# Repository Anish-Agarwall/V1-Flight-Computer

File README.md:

# V1 Flight Computer

An STM32-based rocket flight computer designed by Anish Agarwal and Aidan Gonzales. This repository contains the KiCad schematics and PCB layout, custom component libraries, and firmware developed in STM32CubeIDE.

The board brings together flight sensing, GPS, LoRa telemetry, microSD logging, main and drogue deployment channels, and a servo output for airbrakes.

## Hardware

The PCB uses four copper layers and an STM32F446RE microcontroller.

| Component | Purpose | Firmware interface |
| --- | --- | --- |
| BMI088 | Accelerometer and gyroscope | I2C1 |
| BMP388 | Pressure, temperature, and barometric altitude | I2C1 |
| LIS3MDL | Magnetometer | I2C1 |
| u-blox NEO-M9N | GPS | USART6 |
| E22-900MM22S | LoRa telemetry | SPI1 |
| W25Q128JVS | 128-Mbit external flash | SPI2 |
| microSD | CSV data logging | SPI3 |

The design also includes battery-voltage and deployment-continuity sensing, a buzzer, a heartbeat LED, and USB-C. The active firmware uses the BMI088; a BMI330 driver is also included in the source tree.

## Firmware

The application is written in C using the STM32 HAL and FatFs. Most of the flight logic is in [`main.c`](V1_STM32/Core/Src/main.c), with separate drivers for the sensors, GPS, radio, SD card, and flash.

The main loop handles:

- Sensor readings and flight-state updates on a nominal 50 ms interval.
- Ground-relative barometric altitude, filtered altitude, and estimated vertical velocity.
- Launch and apogee detection, followed by drogue and main deployment states.
- GPS stream processing and LoRa packet transmission, scheduled at 200 ms intervals.
- Buffered CSV logging to the SD card.
- Servo airbrake control using predicted apogee and a PD controller, enabled seven seconds after launch.

Flight thresholds, deployment settings, and servo limits are defined in `main.c`. The airbrake target and controller gains are inside `Task_Airbrakes()`.

### Data logging

On startup, the firmware selects a numbered log file such as `LOG_0.CSV` or `LOG_1.CSV`. Logged fields include altitude, pressure, temperature, flight state, airbrake output, filtered altitude and velocity, magnetometer readings, and GPS data.

Battery and continuity columns are present, but their periodic sampling task is currently commented out. Data rows also include a Unix timestamp that is missing from the startup CSV header.

The flash driver and a binary logging routine are included, but the current main loop uses the SD logging path and does not call the flash-log flush routine.

## Repository layout

| Path | Contents |
| --- | --- |
| `V1_Hardware/` | KiCad project, schematics, PCB layout, footprints, and 3D models |
| `V1_STM32/` | STM32CubeIDE project and CubeMX configuration |
| `V1_STM32/Core/Src/` | Main application and device drivers |
| `V1_STM32/Core/Inc/` | Headers, telemetry packet definitions, and buffer utilities |
| `V1_STM32/FATFS/` | FatFs configuration and SD disk interface |
| `V1_STM32/Drivers/` | STM32 HAL and CMSIS files |
| `LRA_Parts/` | Component symbols, footprints, and models |

## Opening the project

### Hardware

1. Open `V1_Hardware/V1.kicad_pro` in KiCad. The checked-in design files were saved with KiCad 10.0.
2. In **Preferences → Configure Paths**, set `LRA_PARTS` to the repository's `LRA_Parts` directory.
3. Check the project symbol-library table. Some entries still use absolute Windows paths and need to be pointed to your local copies. Entries that point to a directory should be updated to the corresponding `.kicad_sym` file.

The root schematic is `V1.kicad_sch`. Separate sheets cover power, deployment circuitry, USB-C, memory, GPS/telemetry, and sensors.

### Firmware

1. In STM32CubeIDE, choose **File → Import → General → Existing Projects into Workspace** and select `V1_STM32`.
2. Build the imported project. The repository includes the HAL, CMSIS, and FatFs sources.
3. Use an ST-LINK connection over SWD to program and debug the board. Check the probe settings in the included `V1 Debug.launch` configuration for your setup.

`V1.ioc` contains the CubeMX configuration and records STM32CubeMX 6.14.1 with STM32CubeF4 firmware package V1.28.3. Check the existing application code before regenerating peripheral initialization code.

## Development notes

Some earlier bring-up routines and alternate logging paths remain in the source. Follow the active calls in `main.c` when checking current behavior; a few older comments describe previous pin assignments or hardware revisions.

The `LANDED` state currently follows the main-deployment timer rather than a separate touchdown detector.

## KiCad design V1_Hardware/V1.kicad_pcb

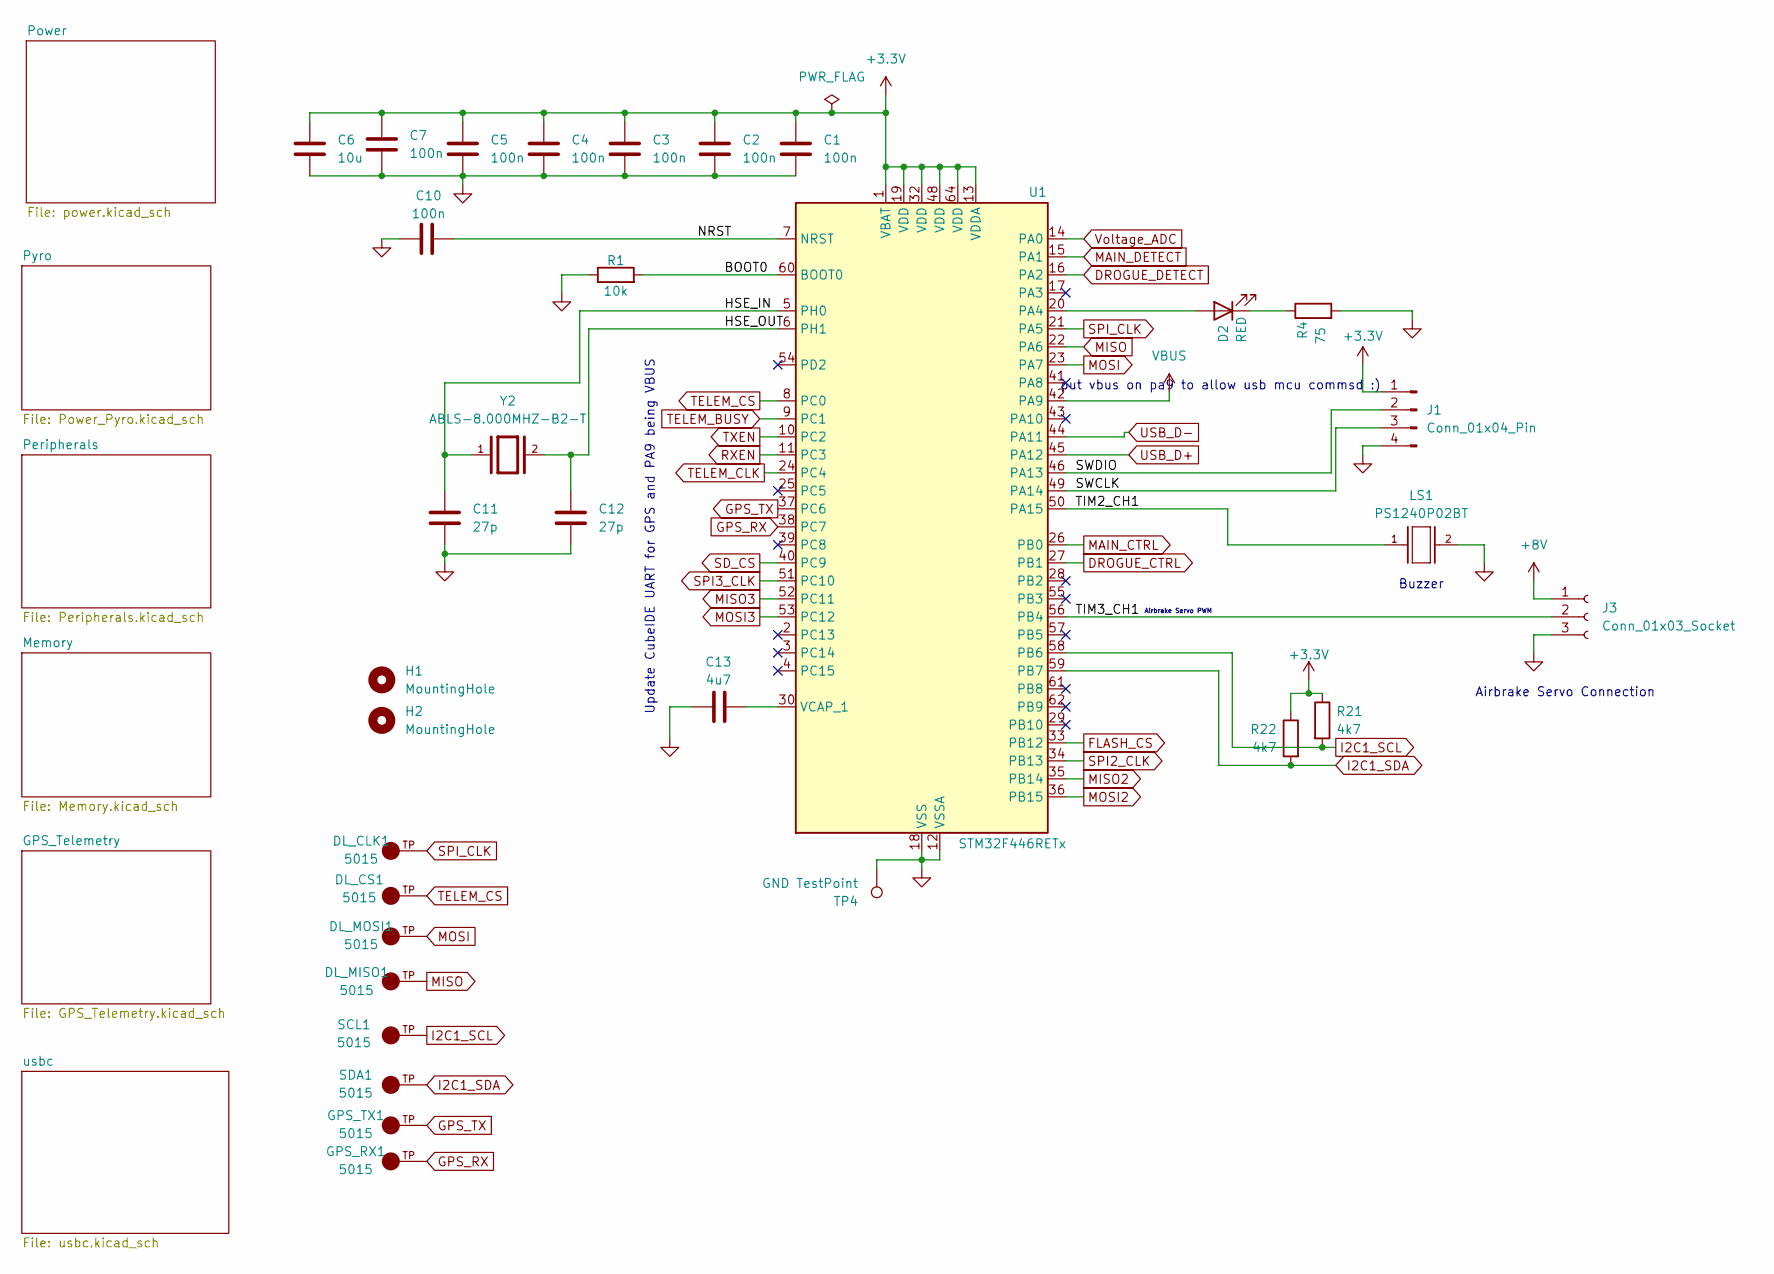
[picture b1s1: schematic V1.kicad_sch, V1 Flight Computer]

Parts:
C1, C2, C3, C4, C5, C7, C10: 100n; C_0603_1608Metric_Pad1.08x0.95mm_HandSolder
C6: 10u; C_0603_1608Metric_Pad1.08x0.95mm_HandSolder
C11, C12: 27p; C_0603_1608Metric_Pad1.08x0.95mm_HandSolder
C13: 4u7; C_0603_1608Metric_Pad1.08x0.95mm_HandSolder
D2: RED; LED_1206_3216Metric_Pad1.42x1.75mm_HandSolder
DL_CLK1: 5015; PARTREV F
DL_CS1: 5015; PARTREV F
DL_MISO1: 5015; PARTREV F
DL_MOSI1: 5015; PARTREV F
GPS_RX1: 5015; PARTREV F
GPS_TX1: 5015; PARTREV F
H1, H2: MountingHole; MountingHole_3.2mm_M3
J1: Conn_01x04_Pin; PinHeader_1x04_P2.54mm_Vertical
J3: Conn_01x03_Socket; Molex_Nano-Fit_105309-xx03_1x03_P2.50mm_Vertical
LS1: PS1240P02BT
R1: 10k; R_0603_1608Metric_Pad0.98x0.95mm_HandSolder
R4: 75; R_0603_1608Metric_Pad0.98x0.95mm_HandSolder
R21, R22: 4k7; R_0603_1608Metric_Pad0.98x0.95mm_HandSolder
SCL1: 5015; PARTREV F
SDA1: 5015; PARTREV F
TP4: GND TestPoint; TestPoint_Pad_D2.0mm
U1: STM32F446RETx; LQFP-64_10x10mm_P0.5mm
Y2: ABLS-8.000MHZ-B2-T; PARTREV 02.16.2021

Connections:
+3.3V: C1.1, C2.1, C3.1, C4.1, C5.1, C6.1, C7.1, J1.1, R21.1, R22.1, U1.1 (VBAT), U1.13 (VDDA), U1.19 (VDD), U1.32 (VDD), U1.48 (VDD), U1.64 (VDD); also elsewhere on the board
+8V: J3.1; also elsewhere on the board
/BOOT0: R1.2, U1.60 (BOOT0)
/HSE_IN: C11.1, U1.5 (PH0), Y2.1
/HSE_OUT: C12.1, U1.6 (PH1), Y2.2
/NRST: C10.2, U1.7 (NRST)
/SWCLK: J1.3, U1.49 (PA14)
/SWDIO: J1.2, U1.46 (PA13)
/TIM2_CH1: LS1.1, U1.50 (PA15)
/TIM3_CH1: J3.2, U1.56 (PB4)
DROGUE_CTRL: U1.27 (PB1); also elsewhere on the board
DROGUE_DETECT: U1.16 (PA2); also elsewhere on the board
FLASH_CS: U1.33 (PB12); also elsewhere on the board
GND: C1.2, C2.2, C3.2, C4.2, C5.2, C6.2, C7.2, C10.1, C11.2, C12.2, C13.1, J1.4, J3.3, LS1.2, R1.1, R4.2, TP4.1 (1_1), U1.12 (VSSA), U1.18 (VSS), U1.31 (VSS), U1.47 (VSS), U1.63 (VSS); also elsewhere on the board
GPS_RX: GPS_RX1.TP, U1.38 (PC7); also elsewhere on the board
GPS_TX: GPS_TX1.TP, U1.37 (PC6); also elsewhere on the board
I2C1_SCL: R21.2, SCL1.TP, U1.58 (PB6); also elsewhere on the board
I2C1_SDA: R22.2, SDA1.TP, U1.59 (PB7); also elsewhere on the board
MAIN_CTRL: U1.26 (PB0); also elsewhere on the board
MAIN_DETECT: U1.15 (PA1); also elsewhere on the board
MISO: DL_MISO1.TP, U1.22 (PA6); also elsewhere on the board
MISO2: U1.35 (PB14); also elsewhere on the board
MISO3: U1.52 (PC11); also elsewhere on the board
MOSI: DL_MOSI1.TP, U1.23 (PA7); also elsewhere on the board
MOSI2: U1.36 (PB15); also elsewhere on the board
MOSI3: U1.53 (PC12); also elsewhere on the board
unnamed: D2.2 (A), U1.20 (PA4)
unnamed: D2.1 (K), R4.1
unnamed: C13.2, U1.30 (VCAP_1)
RXEN: U1.11 (PC3); also elsewhere on the board
SD_CS: U1.40 (PC9); also elsewhere on the board
SPI2_CLK: U1.34 (PB13); also elsewhere on the board
SPI3_CLK: U1.51 (PC10); also elsewhere on the board
SPI_CLK: DL_CLK1.TP, U1.21 (PA5); also elsewhere on the board
TELEM_BUSY: U1.9 (PC1); also elsewhere on the board
TELEM_CLK: U1.24 (PC4); also elsewhere on the board
TELEM_CS: DL_CS1.TP, U1.8 (PC0); also elsewhere on the board
TXEN: U1.10 (PC2); also elsewhere on the board
USB_D+: U1.45 (PA12); also elsewhere on the board
USB_D-: U1.44 (PA11); also elsewhere on the board
VBUS: U1.42 (PA9); also elsewhere on the board
Voltage_ADC: U1.14 (PA0); also elsewhere on the board

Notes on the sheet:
Update CubeIDE UART for GPS and PA9 being VBUS
put vbus on pa9 to allow usb mcu commsd :)
Airbrake Servo Connection
Airbrake Servo PWM
Buzzer

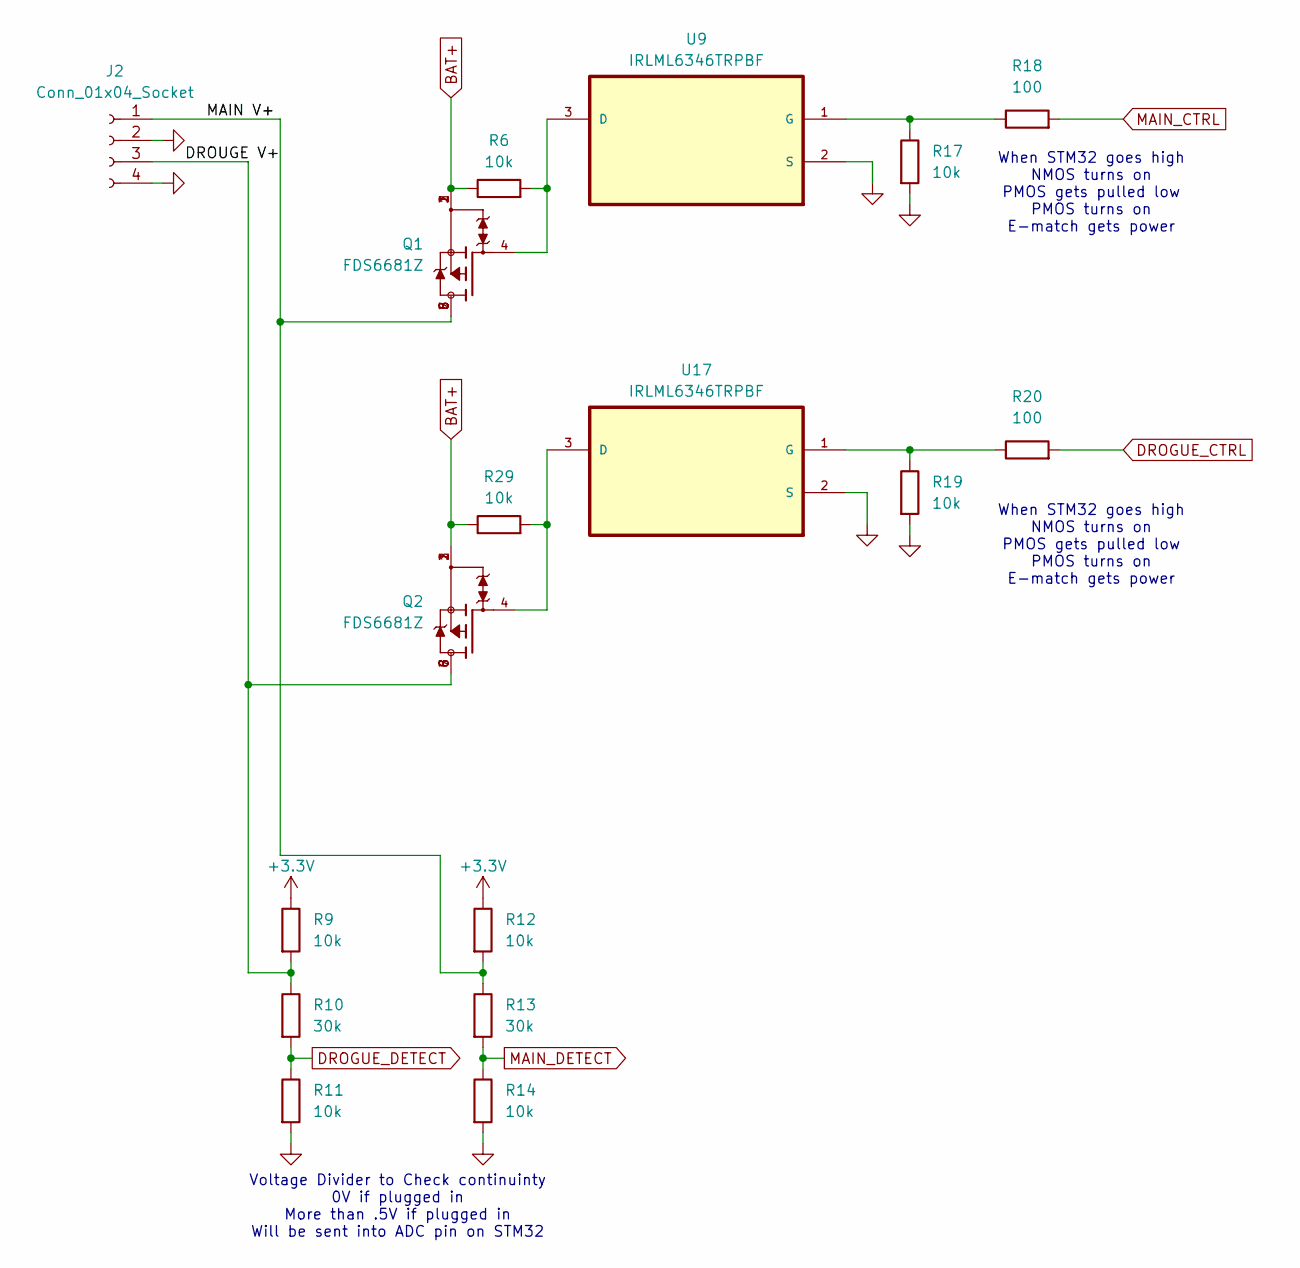
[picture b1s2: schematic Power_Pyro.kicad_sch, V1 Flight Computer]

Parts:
J2: Conn_01x04_Socket; Molex_Nano-Fit_105309-xx04_1x04_P2.50mm_Vertical
Q1, Q2: FDS6681Z
R6, R9, R11, R12, R14, R17, R19, R29: 10k; R_0603_1608Metric_Pad0.98x0.95mm_HandSolder
R10, R13: 30k; R_0603_1608Metric_Pad0.98x0.95mm_HandSolder
R18, R20: 100; R_0603_1608Metric_Pad0.98x0.95mm_HandSolder
U9, U17: IRLML6346TRPBF; MPN IRLML6346TRPBF

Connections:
+3.3V: R9.1, R12.1; also elsewhere on the board
/Pyro/DROUGE V+: J2.3, Q2.5, Q2.6, Q2.7, Q2.8, R9.2, R10.1
/Pyro/MAIN V+: J2.1, Q1.5, Q1.6, Q1.7, Q1.8, R12.2, R13.1
BAT+: Q1.1, Q1.2, Q1.3, Q2.1, Q2.2, Q2.3, R6.1, R29.1; also elsewhere on the board
DROGUE_CTRL: R20.2; also elsewhere on the board
DROGUE_DETECT: R10.2, R11.1; also elsewhere on the board
GND: J2.2, J2.4, R11.2, R14.2, R17.2, R19.2, U9.2 (S), U17.2 (S); also elsewhere on the board
MAIN_CTRL: R18.2; also elsewhere on the board
MAIN_DETECT: R13.2, R14.1; also elsewhere on the board
unnamed: Q1.4, R6.2, U9.3 (D)
unnamed: R17.1, R18.1, U9.1 (G)
unnamed: Q2.4, R29.2, U17.3 (D)
unnamed: R19.1, R20.1, U17.1 (G)

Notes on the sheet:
Voltage Divider to Check continuinty 0V if plugged in More than .5V if plugged in Will be sent into ADC pin on STM32
When STM32 goes high NMOS turns on PMOS gets pulled low PMOS turns on E-match gets power

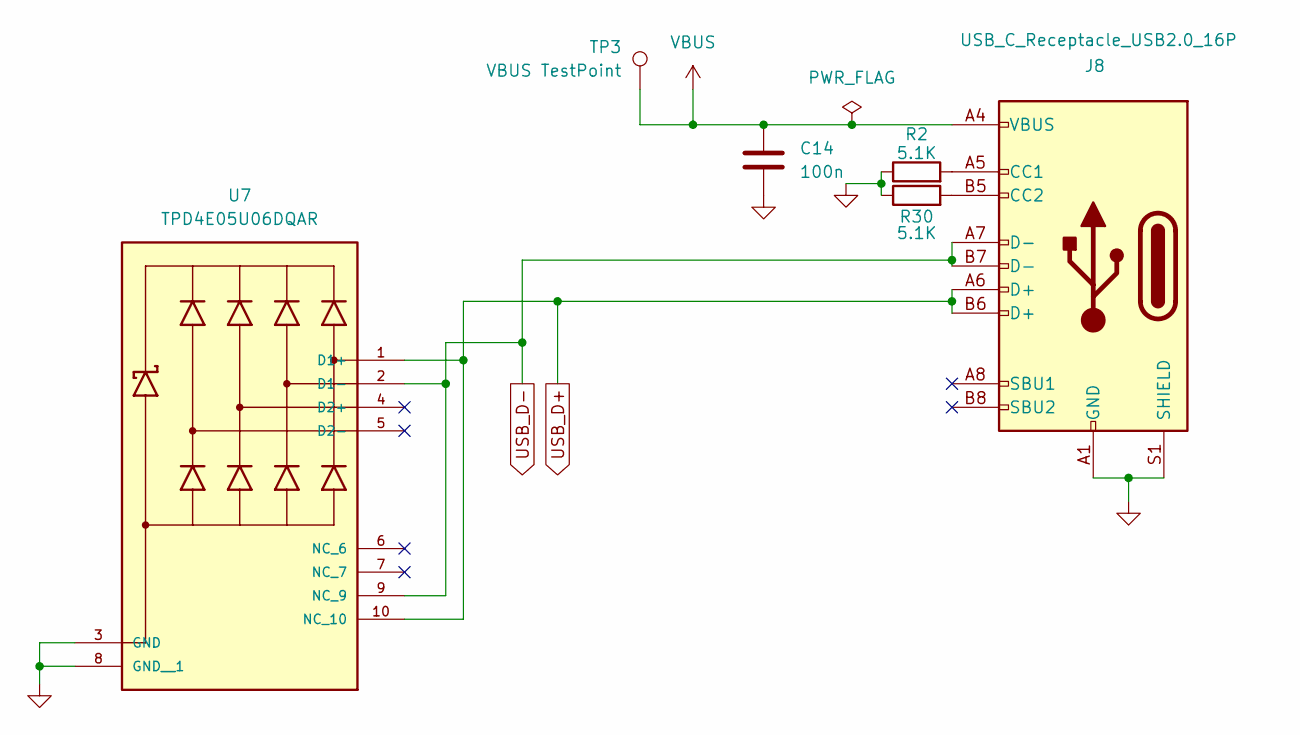
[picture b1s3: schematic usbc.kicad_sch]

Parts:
C14: 100n; C_0603_1608Metric_Pad1.08x0.95mm_HandSolder
J8: USB_C_Receptacle_USB2.0_16P; USB_C_Receptacle_GCT_USB4105-xx-A_16P_TopMnt_Horizontal
R2, R30: 5.1K; R_0603_1608Metric_Pad0.98x0.95mm_HandSolder
TP3: VBUS TestPoint; TestPoint_Pad_D2.0mm
U7: TPD4E05U06DQAR; PARTREV N

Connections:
GND: C14.1, J8.A1 (GND), J8.A12 (GND), J8.B1 (GND), J8.B12 (GND), J8.S1 (SHIELD), R2.1, R30.1, U7.3 (GND), U7.8 (GND__1); also elsewhere on the board
unnamed: J8.A5 (CC1), R2.2
unnamed: J8.B5 (CC2), R30.2
USB_D+: J8.A6 (D+), J8.B6 (D+), U7.1 (D1+), U7.10 (NC_10); also elsewhere on the board
USB_D-: J8.A7 (D-), J8.B7 (D-), U7.2 (D1-), U7.9 (NC_9); also elsewhere on the board
VBUS: C14.2, J8.A4 (VBUS), J8.A9 (VBUS), J8.B4 (VBUS), J8.B9 (VBUS), TP3.1 (1_1); also elsewhere on the board

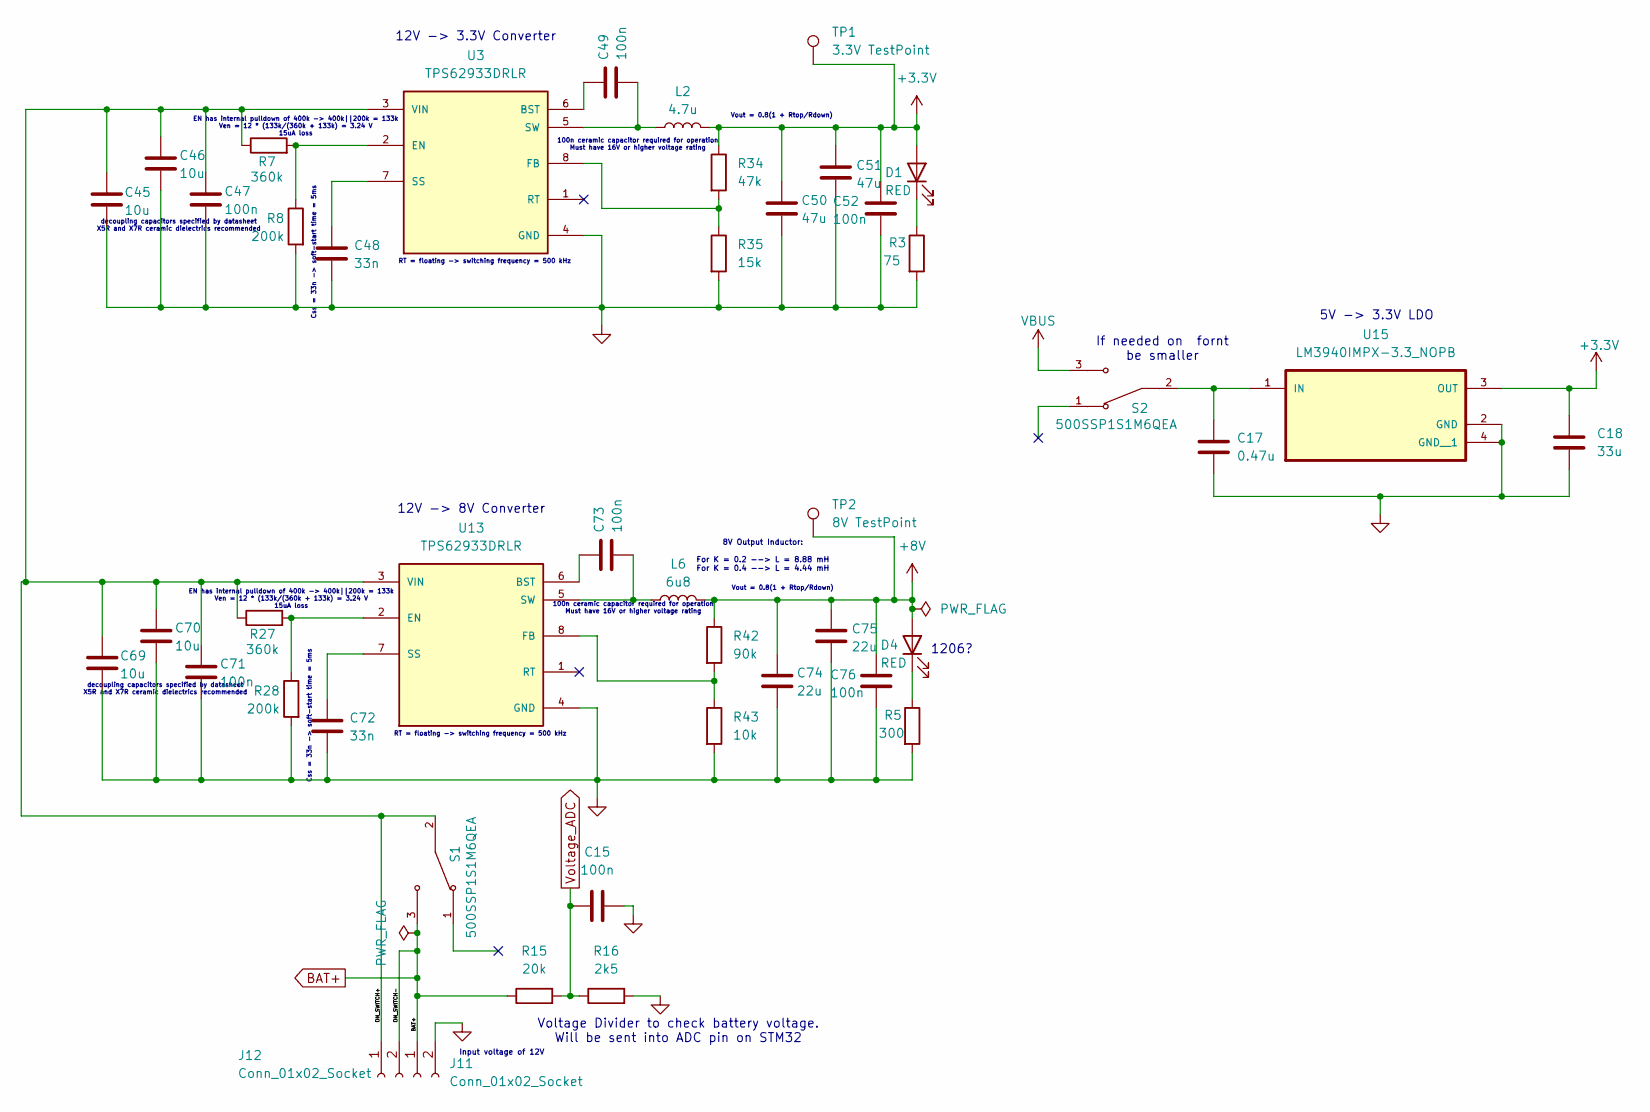
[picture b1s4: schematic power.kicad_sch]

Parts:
C15, C47, C49, C52, C71, C73, C76: 100n; C_0603_1608Metric_Pad1.08x0.95mm_HandSolder
C17: 0.47u; C_0603_1608Metric_Pad1.08x0.95mm_HandSolder
C18: 33u; C_0805_2012Metric_Pad1.18x1.45mm_HandSolder
C45, C46, C69, C70: 10u; C_0603_1608Metric_Pad1.08x0.95mm_HandSolder
C48, C72: 33n; C_0603_1608Metric_Pad1.08x0.95mm_HandSolder
C50, C51: 47u; C_0805_2012Metric_Pad1.18x1.45mm_HandSolder
C74, C75: 22u; C_0603_1608Metric_Pad1.08x0.95mm_HandSolder
D1, D4: RED; LED_1206_3216Metric_Pad1.42x1.75mm_HandSolder
J11, J12: Conn_01x02_Socket; Molex_Nano-Fit_105309-xx02_1x02_P2.50mm_Vertical
L2: 4.7u; L_1210_3225Metric_Pad1.42x2.65mm_HandSolder
L6: 6u8; L_1210_3225Metric_Pad1.42x2.65mm_HandSolder
R3: 75; R_0603_1608Metric_Pad0.98x0.95mm_HandSolder
R5: 300; R_0603_1608Metric_Pad0.98x0.95mm_HandSolder
R7, R27: 360k; R_0603_1608Metric_Pad0.98x0.95mm_HandSolder
R8, R28: 200k; R_0603_1608Metric_Pad0.98x0.95mm_HandSolder
R15: 20k; R_0603_1608Metric_Pad0.98x0.95mm_HandSolder
R16: 2k5; R_0603_1608Metric_Pad0.98x0.95mm_HandSolder
R34: 47k; R_0603_1608Metric_Pad0.98x0.95mm_HandSolder
R35: 15k; R_0603_1608Metric_Pad0.98x0.95mm_HandSolder
R42: 90k; R_0805_2012Metric_Pad1.20x1.40mm_HandSolder
R43: 10k; R_0603_1608Metric_Pad0.98x0.95mm_HandSolder
S1, S2: 500SSP1S1M6QEA; PARTREV D
TP1: 3.3V TestPoint; TestPoint_Pad_D2.0mm
TP2: 8V TestPoint; TestPoint_Pad_D2.0mm
U3, U13: TPS62933DRLR; PARTREV D
U15: LM3940IMPX-3.3_NOPB

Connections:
+3.3V: C18.1, C50.1, C51.1, C52.1, D1.2 (A), L2.2, R34.1, TP1.1 (1_1), U15.3 (OUT); also elsewhere on the board
+8V: C74.1, C75.1, C76.1, D4.2 (A), L6.2, R42.1, TP2.1 (1_1); also elsewhere on the board
/Power/ON_SWITCH+: C45.1, C46.1, C47.1, C69.1, C70.1, C71.1, J12.1, R7.1, R27.1, S1.2, U3.3 (VIN), U13.3 (VIN)
BAT+: J11.1, J12.2, R15.1, S1.3; also elsewhere on the board
GND: C15.2, C17.2, C18.2, C45.2, C46.2, C47.2, C48.2, C50.2, C51.2, C52.2, C69.2, C70.2, C71.2, C72.2, C74.2, C75.2, C76.2, J11.2, R3.2, R5.2, R8.2, R16.2, R28.2, R35.2, R43.2, U3.4 (GND), U13.4 (GND), U15.2 (GND), U15.4 (GND__1); also elsewhere on the board
unnamed: D1.1 (K), R3.1
unnamed: D4.1 (K), R5.1
unnamed: C49.1, U3.6 (BST)
unnamed: R7.2, R8.1, U3.2 (EN)
unnamed: R34.2, R35.1, U3.8 (FB)
unnamed: C48.1, U3.7 (SS)
unnamed: C49.2, L2.1, U3.5 (SW)
unnamed: C73.1, U13.6 (BST)
unnamed: R27.2, R28.1, U13.2 (EN)
unnamed: R42.2, R43.1, U13.8 (FB)
unnamed: C72.1, U13.7 (SS)
unnamed: C73.2, L6.1, U13.5 (SW)
unnamed: C17.1, S2.2, U15.1 (IN)
VBUS: S2.3; also elsewhere on the board
Voltage_ADC: C15.1, R15.2, R16.1; also elsewhere on the board

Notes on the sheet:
8V Output Inductor: For K = 0.2 --> L = 8.88 mH For K = 0.4 --> L = 4.44 mH
12V -> 8V Converter
Vout = 0.8(1 + Rtop/Rdown)
Voltage Divider to check battery voltage. Will be sent into ADC pin on STM32
100n ceramic capacitor required for operation Must have 16V or higher voltage rating
Css = 33n -> soft-start time = 5ms
EN has internal pulldown of 400k -> 400k||200k = 133k Ven = 12 * (133k/(360k + 133k) = 3.24 V 15uA loss
RT = floating -> switching frequency = 500 kHz
5V -> 3.3V LDO
Input voltage of 12V
1206?
12V -> 3.3V Converter
decoupling capacitors specified by datasheet X5R and X7R ceramic dielectrics recommended
If needed on fornt be smaller

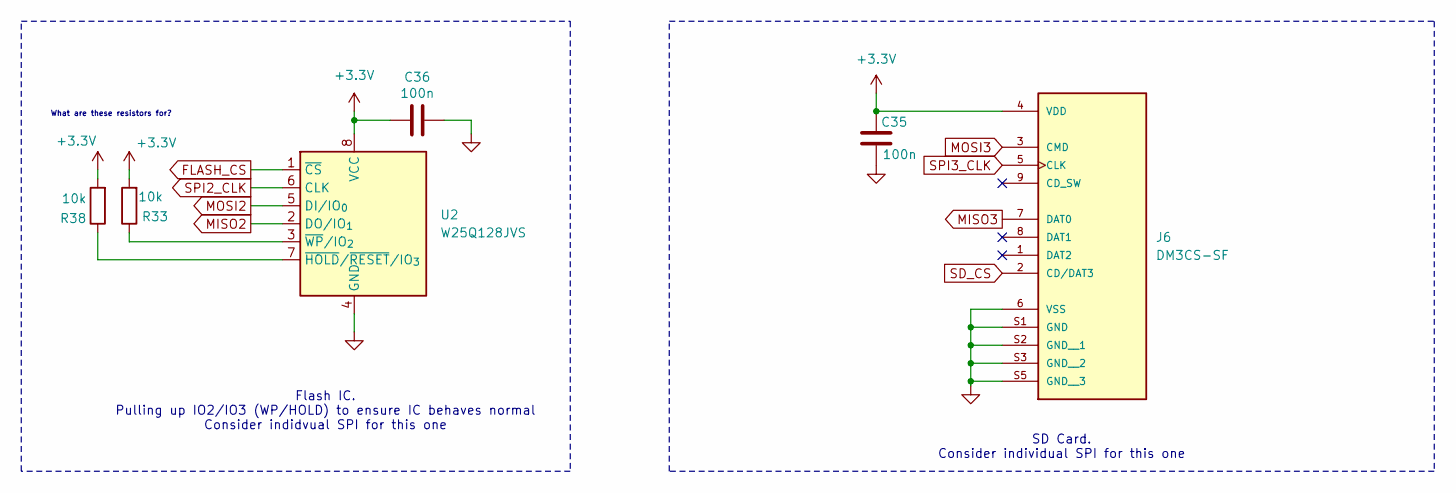
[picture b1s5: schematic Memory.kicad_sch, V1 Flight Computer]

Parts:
C35, C36: 100n; C_0603_1608Metric_Pad1.08x0.95mm_HandSolder
J6: DM3CS-SF; PARTREV n/a
R33, R38: 10k; R_0603_1608Metric_Pad0.98x0.95mm_HandSolder
U2: W25Q128JVS; SOIC-8_5.3x5.3mm_P1.27mm

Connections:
+3.3V: C35.2, C36.1, J6.4 (VDD), R33.2, R38.2, U2.8 (VCC); also elsewhere on the board
FLASH_CS: U2.1 (~CS); also elsewhere on the board
GND: C35.1, C36.2, J6.6 (VSS), J6.S1 (GND), J6.S2 (GND__1), J6.S3 (GND__2), J6.S5 (GND__3), U2.4 (GND); also elsewhere on the board
MISO2: U2.2 (DO/IO_{1}); also elsewhere on the board
MISO3: J6.7 (DAT0); also elsewhere on the board
MOSI2: U2.5 (DI/IO_{0}); also elsewhere on the board
MOSI3: J6.3 (CMD); also elsewhere on the board
unnamed: R38.1, U2.7 (~HOLD/~RESET/IO_{3})
unnamed: R33.1, U2.3 (~WP/IO_{2})
SD_CS: J6.2 (CD/DAT3); also elsewhere on the board
SPI2_CLK: U2.6 (CLK); also elsewhere on the board
SPI3_CLK: J6.5 (CLK); also elsewhere on the board

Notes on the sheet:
Flash IC. Pulling up IO2/IO3 (WP/HOLD) to ensure IC behaves normal Consider indidvual SPI for this one
SD Card. Consider individual SPI for this one
What are these resistors for?

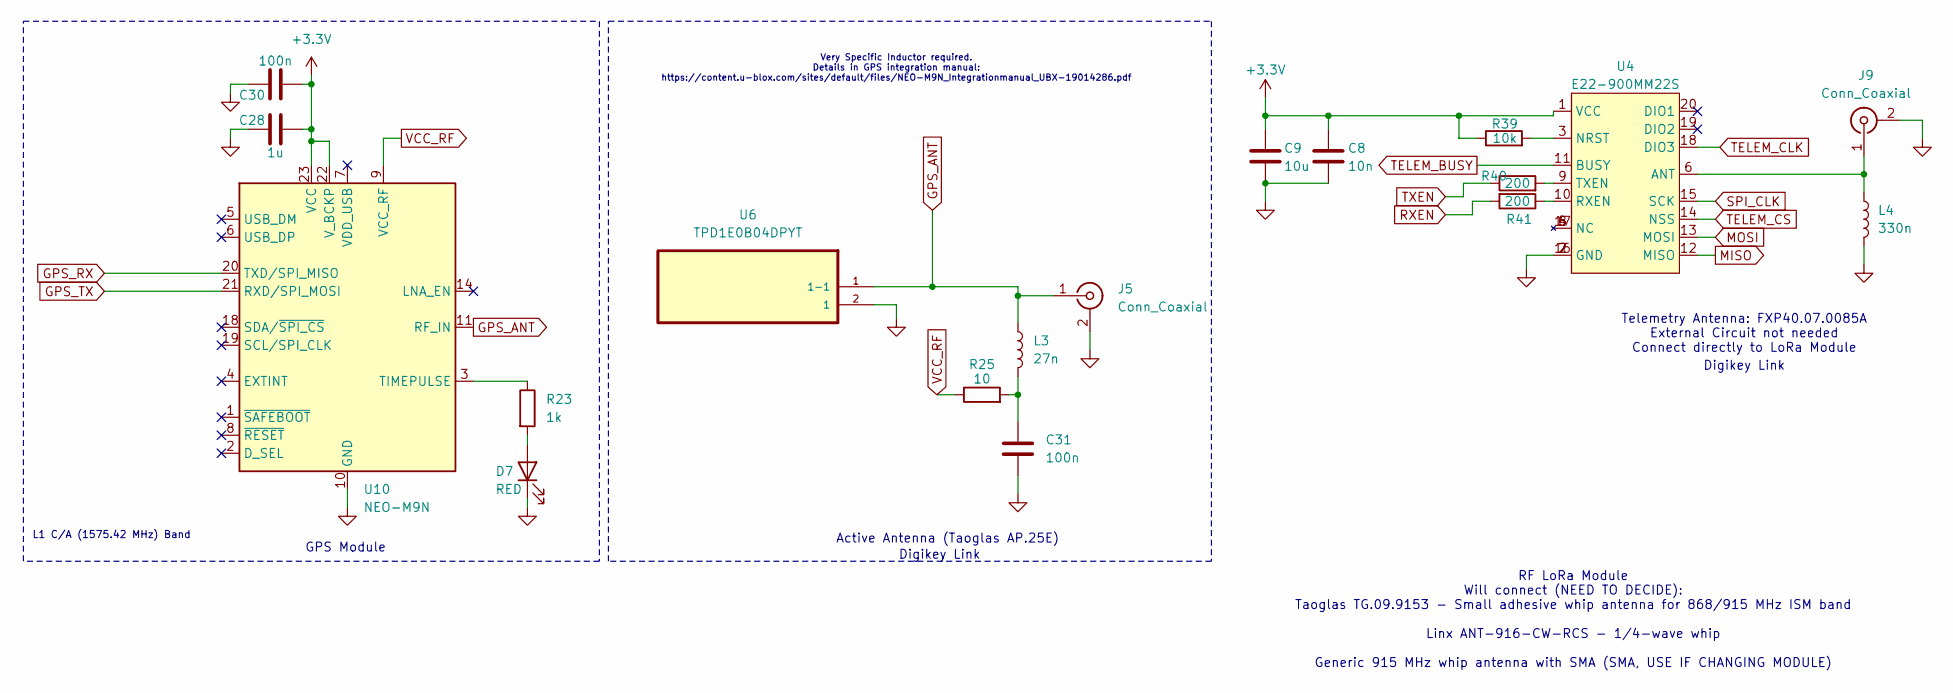
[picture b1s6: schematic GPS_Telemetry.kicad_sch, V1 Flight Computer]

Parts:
C8: 10n; C_0603_1608Metric_Pad1.08x0.95mm_HandSolder
C9: 10u; C_0603_1608Metric_Pad1.08x0.95mm_HandSolder
C28: 1u; C_0603_1608Metric_Pad1.08x0.95mm_HandSolder
C30, C31: 100n; C_0603_1608Metric_Pad1.08x0.95mm_HandSolder
D7: RED; LED_1206_3216Metric_Pad1.42x1.75mm_HandSolder
J5, J9: Conn_Coaxial; U.FL_Molex_MCRF_73412-0110_Vertical
L3: 27n; L_1008_2520Metric_Pad1.43x2.20mm_HandSolder
L4: 330n; L_1008_2520Metric_Pad1.43x2.20mm_HandSolder
R23: 1k; R_0603_1608Metric_Pad0.98x0.95mm_HandSolder
R25: 10; R_0603_1608Metric_Pad0.98x0.95mm_HandSolder
R39: 10k; R_0603_1608Metric_Pad0.98x0.95mm_HandSolder
R40, R41: 200; R_0603_1608Metric_Pad0.98x0.95mm_HandSolder
U4: E22-900MM22S
U6: TPD1E0B04DPYT
U10: NEO-M9N; ublox_NEO

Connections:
+3.3V: C8.1, C9.1, C28.2, C30.2, R39.1, U4.1 (VCC), U10.22 (V_BCKP), U10.23 (VCC); also elsewhere on the board
GND: C8.2, C9.2, C28.1, C30.1, C31.2, D7.1 (K), J5.2 (Ext), J9.2 (Ext), L4.2, U4.2 (GND), U4.7 (GND), U4.16 (GND), U6.2 (1), U10.10 (GND), U10.12 (GND), U10.13 (GND), U10.24 (GND); also elsewhere on the board
GPS_ANT: J5.1 (In), L3.1, U6.1 (1-1), U10.11 (RF_IN)
GPS_RX: U10.20 (TXD/SPI_MISO); also elsewhere on the board
GPS_TX: U10.21 (RXD/SPI_MOSI); also elsewhere on the board
MISO: U4.12 (MISO); also elsewhere on the board
MOSI: U4.13 (MOSI); also elsewhere on the board
unnamed: C31.1, L3.2, R25.2
unnamed: D7.2 (A), R23.2
unnamed: J9.1 (In), L4.1, U4.6 (ANT)
unnamed: R39.2, U4.3 (NRST)
unnamed: R41.1, U4.10 (RXEN)
unnamed: R40.2, U4.9 (TXEN)
unnamed: R23.1, U10.3 (TIMEPULSE)
RXEN: R41.2; also elsewhere on the board
SPI_CLK: U4.15 (SCK); also elsewhere on the board
TELEM_BUSY: U4.11 (BUSY); also elsewhere on the board
TELEM_CLK: U4.18 (DIO3); also elsewhere on the board
TELEM_CS: U4.14 (NSS); also elsewhere on the board
TXEN: R40.1; also elsewhere on the board
VCC_RF: R25.1, U10.9 (VCC_RF)

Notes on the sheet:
RF LoRa Module Will connect (NEED TO DECIDE): Taoglas TG.09.9153 - Small adhesive whip antenna for 868/915 MHz ISM band Linx ANT-916-CW-RCS - 1/4-wave whip Generic 915 MHz whip antenna with SMA (SMA, USE IF CHANGING MODULE)
Active Antenna (Taoglas AP.25E)
L1 C/A (1575.42 MHz) Band
Digikey Link
GPS Module
Very Specific Inductor required. Details in GPS integration manual: https://content.u-blox.com/sites/default/files/NEO-M9N_Integrationmanual_UBX-19014286.pdf
Telemetry Antenna: FXP40.07.0085A External Circuit not needed Connect directly to LoRa Module

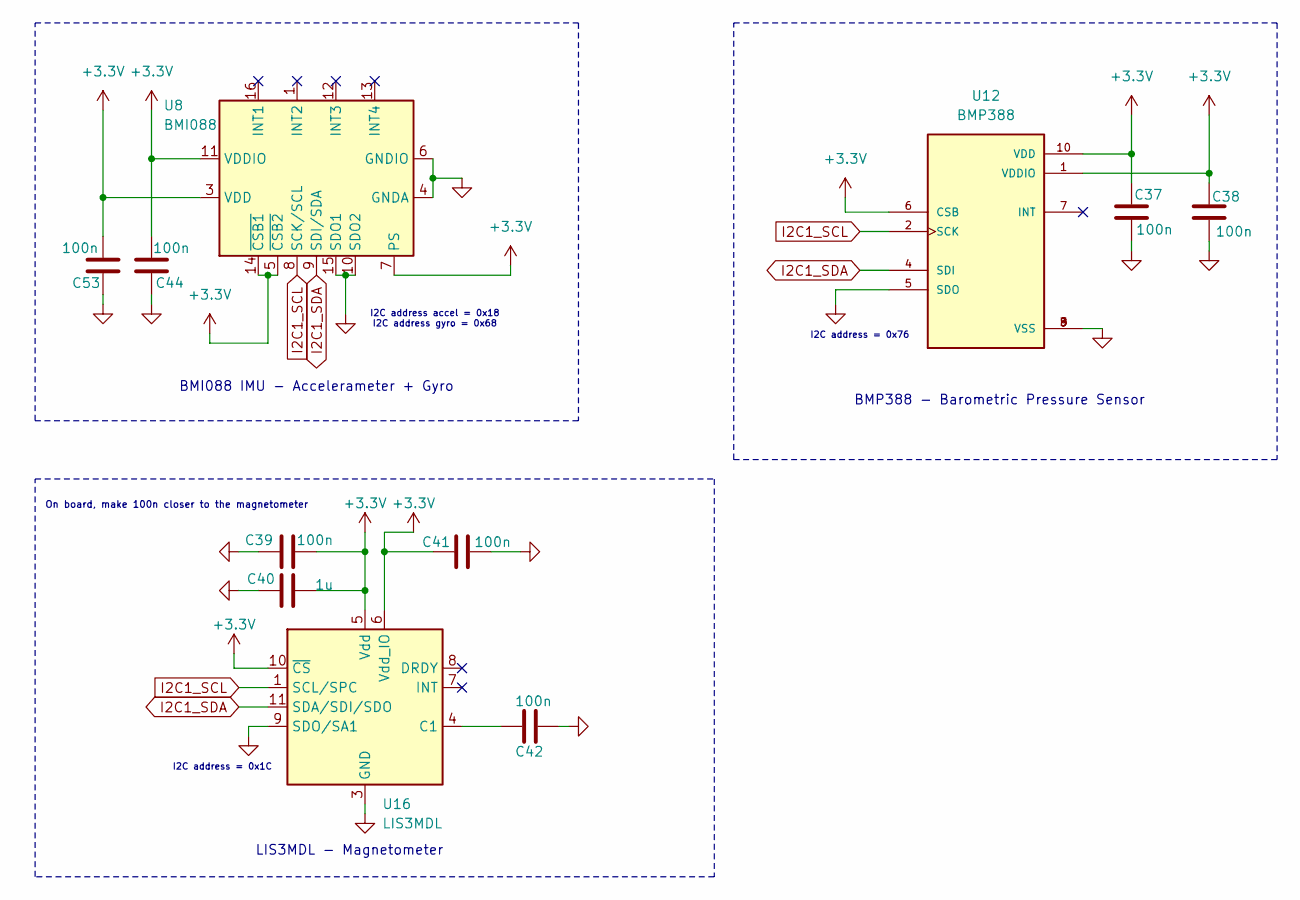
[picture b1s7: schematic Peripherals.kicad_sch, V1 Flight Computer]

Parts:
C37, C38, C39, C41, C42, C44, C53: 100n; C_0603_1608Metric_Pad1.08x0.95mm_HandSolder
C40: 1u; C_0603_1608Metric_Pad1.08x0.95mm_HandSolder
U8: BMI088; Bosch_LGA-16_4.5x3mm_P0.5mm_LayoutBorder7x1y_ClockwisePinNu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
U12: BMP388; PARTREV 1.1
U16: LIS3MDL; LGA-12_2x2mm_P0.5mm

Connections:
+3.3V: C37.1, C38.1, C39.2, C40.2, C41.2, C44.2, C53.2, U8.3 (VDD), U8.5 (~CSB2), U8.7 (PS), U8.11 (VDDIO), U8.14 (~CSB1), U12.1 (VDDIO), U12.6 (CSB), U12.10 (VDD), U16.5 (Vdd), U16.6 (Vdd_IO), U16.10 (~CS); also elsewhere on the board
GND: C37.2, C38.2, C39.1, C40.1, C41.1, C42.1, C44.1, C53.1, U8.2 (GNDA), U8.4 (GNDA), U8.6 (GNDIO), U8.10 (SDO2), U8.15 (SDO1), U12.3 (VSS), U12.5 (SDO), U12.8 (VSS), U12.9 (VSS), U16.2 (GND), U16.3 (GND), U16.9 (SDO/SA1), U16.12 (GND); also elsewhere on the board
I2C1_SCL: U8.8 (SCK/SCL), U12.2 (SCK), U16.1 (SCL/SPC); also elsewhere on the board
I2C1_SDA: U8.9 (SDI/SDA), U12.4 (SDI), U16.11 (SDA/SDI/SDO); also elsewhere on the board
unnamed: C42.2, U16.4 (C1)

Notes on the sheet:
LIS3MDL - Magnetometer
I2C address = 0x76
I2C address = 0x1C
I2C address accel = 0x18 I2C address gyro = 0x68
BMI088 IMU - Accelerameter + Gyro
BMP388 - Barometric Pressure Sensor
On board, make 100n closer to the magnetometer

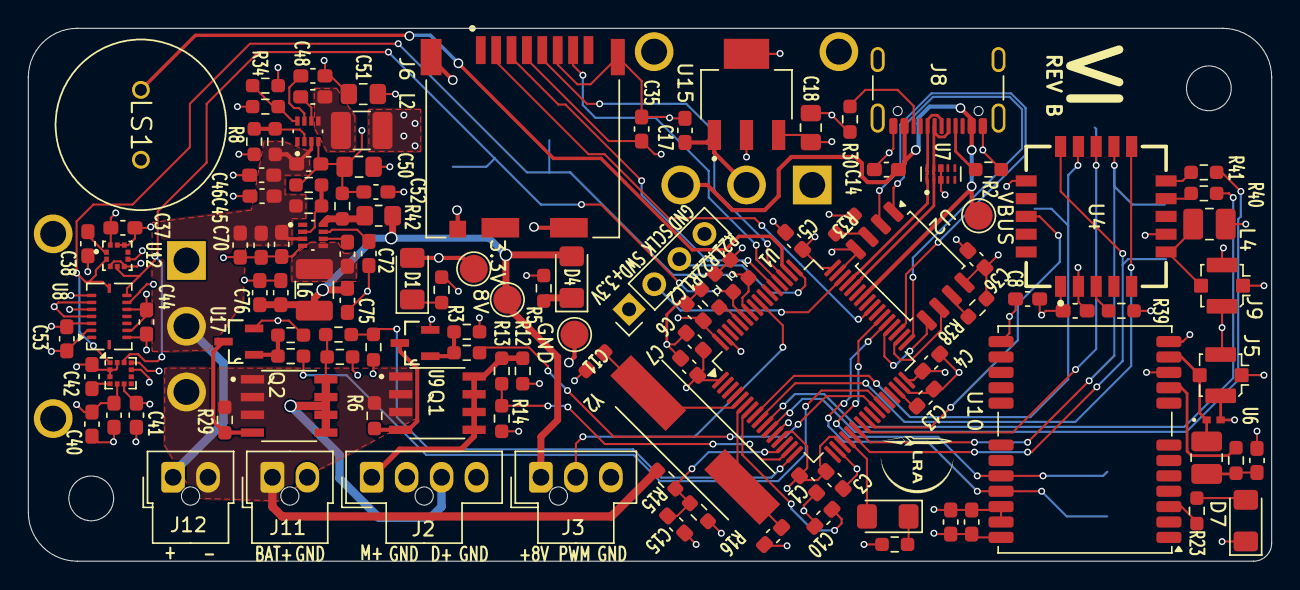
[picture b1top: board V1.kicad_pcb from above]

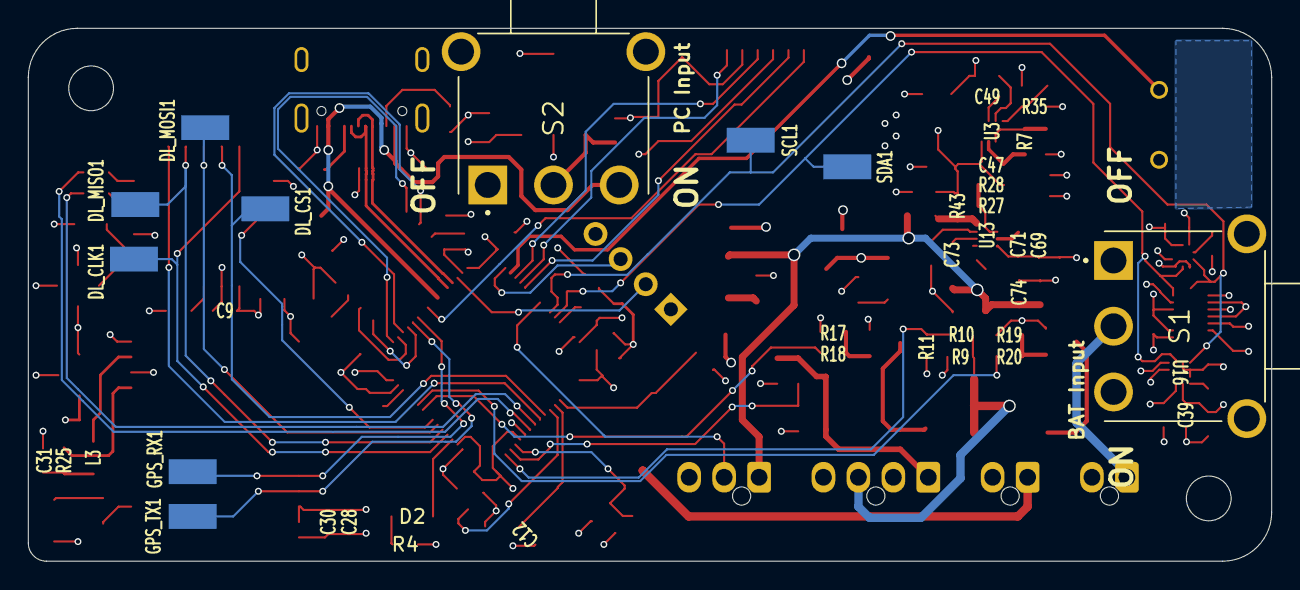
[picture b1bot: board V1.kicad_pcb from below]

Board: 4 copper layers, 88.9 x 38.1 mm, 134 parts (10 on the bottom side), 77 nets.

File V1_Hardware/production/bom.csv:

Designator,Footprint,Quantity,Value,LCSC Part #
"C1, C10, C14, C15, C2, C3, C30, C31, C34, C35, C36, C37, C38, C39, C4, C41, C42, C43, C47, C49, C5, C52, C7, C71, C73, C76",0603,26,100n,
"C11, C12",0603,2,27p,
C13,0603,1,4u7,
C17,0603,1,0.47u,
C18,0805,1,33u,
"C28, C40",0603,2,1u,
"C45, C46, C6, C69, C70, C9",0603,6,10u,
"C48, C72",0603,2,33n,
"C50, C51",0805,2,47u,
"C74, C75",0603,2,22u,
C8,0603,1,10n,
"D1, D2, D4, D7",1206,4,RED,
J1,PinHeader_1x04_P2.54mm_Vertical,1,Conn_01x04_Pin,
"J2, J3",TE_282834-4,2,Screw_Terminal_01x04,
J4,691210910003,1,Screw_Terminal_01x03,
"J5, J9",U.FL_Molex_MCRF_73412-0110_Vertical,2,Conn_Coaxial,
J7,104031-0811,1,104031-0811,
J8,USB_C_Receptacle_GCT_USB4105-xx-A_16P_TopMnt_Horizontal,1,USB_C_Receptacle_USB2.0_16P,
L2,1210,1,4.7u,
L3,1008,1,27n,
L4,1008,1,330n,
L6,1210,1,6u8,
LS1,PS1240P02BT,1,PS1240P02BT,
"Q1, Q2",FDS6681Z,2,FDS6681Z,
"R1, R11, R12, R14, R17, R19, R29, R33, R38, R39, R43, R6, R9",0603,13,10k,
"R10, R13",0603,2,30k,
R15,0603,1,20k,
R16,0603,1,2k5,
"R18, R20",0603,2,100,
"R2, R30",0603,2,5.1K,
"R21, R22",0603,2,4k7,
R23,0603,1,1k,
R25,0603,1,10,
"R27, R7",0603,2,360k,
"R28, R8",0603,2,200k,
"R3, R4",0603,2,75,
R34,0603,1,47k,
R35,0603,1,15k,
"R40, R41",0603,2,200,
R42,0805,1,90k,
R5,0603,1,300,
"S1, S2",500SSP1S1M6QEA,2,500SSP1S1M6QEA,
TP1,TestPoint_Pad_D2.0mm,1,3.3V TestPoint,
TP2,TestPoint_Pad_D2.0mm,1,8V TestPoint,
TP3,TestPoint_Pad_D2.0mm,1,VBUS TestPoint,
TP4,TestPoint_Pad_D2.0mm,1,GND TestPoint,
U1,LQFP-64_10x10mm_P0.5mm,1,STM32F446RETx,
U10,ublox_NEO,1,NEO-M9N,
U12,BMP388,1,BMP388,
"U13, U3",TPS62933DRLR,2,TPS62933DRLR,
U15,LM3940IMPX-3.3_NOPB,1,LM3940IMPX-3.3_NOPB,
U16,LGA-12_2x2mm_P0.5mm,1,LIS3MDL,
"U17, U9",IRLML6346TRPBF,2,IRLML6346TRPBF,IRLML6346TRPBF
U2,SOIC-8_5.3x5.3mm_P1.27mm,1,W25Q128JVS,
U4,E22-900MM22S,1,E22-900MM22S,
U5,BMI330,1,BMI330,
U6,TPD1E0B04DPYT,1,TPD1E0B04DPYT,
U7,TPD4E05U06DQAR,1,TPD4E05U06DQAR,
Y2,ABLS-8.000MHZ-B2-T,1,ABLS-8.000MHZ-B2-T,

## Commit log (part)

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2025-09-01 The first official draft of the schematic
2025-09-01 Renaming folders
2025-09-01 Re-added kicad/hardware files
    Just doing some organization
2025-09-01 organization
2025-09-01 Added all STM32CubeIDE Code
